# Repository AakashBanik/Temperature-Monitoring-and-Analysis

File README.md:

Temperature-Monitoring-and-Analysis

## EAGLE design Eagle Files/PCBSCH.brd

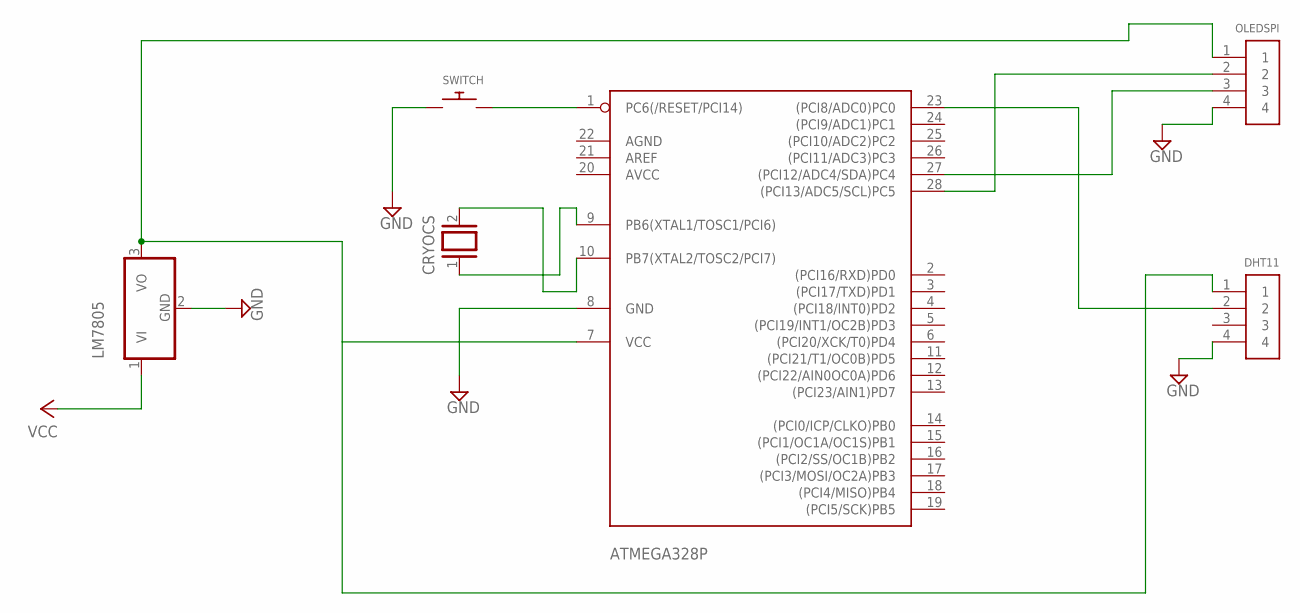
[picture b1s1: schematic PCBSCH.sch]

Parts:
ATMEGA328P: ATMEGA328PROUND; DIL28-3-ROUND
CRYOCS: XTAL/S; QS
DHT11: 1X4-BIG; 1X04-BIG
LM7805: 7805TV; TO220V
OLEDSPI: 1X4-BIG; 1X04-BIG
SWITCH: SWITCH_PUSHBUTTONSOFTTOUCHSMD_SJ; PUSHBUTTON_SMD_SJ

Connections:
GND: ATMEGA328P.8 (GND), DHT11.4, LM7805.2 (GND), OLEDSPI.4, SWITCH.P$1
unnamed: ATMEGA328P.7 (VCC), DHT11.1, LM7805.3 (VO), OLEDSPI.1
unnamed: ATMEGA328P.1 (PC6(/RESET/PCI14)), SWITCH.P$2
unnamed: ATMEGA328P.27 ((PCI12/ADC4/SDA)PC4), OLEDSPI.3
unnamed: ATMEGA328P.28 ((PCI13/ADC5/SCL)PC5), OLEDSPI.2
unnamed: ATMEGA328P.23 ((PCI8/ADC0)PC0), DHT11.2
unnamed: ATMEGA328P.9 (PB6(XTAL1/TOSC1/PCI6)), CRYOCS.1
unnamed: ATMEGA328P.10 (PB7(XTAL2/TOSC2/PCI7)), CRYOCS.2
VCC: LM7805.1 (VI)

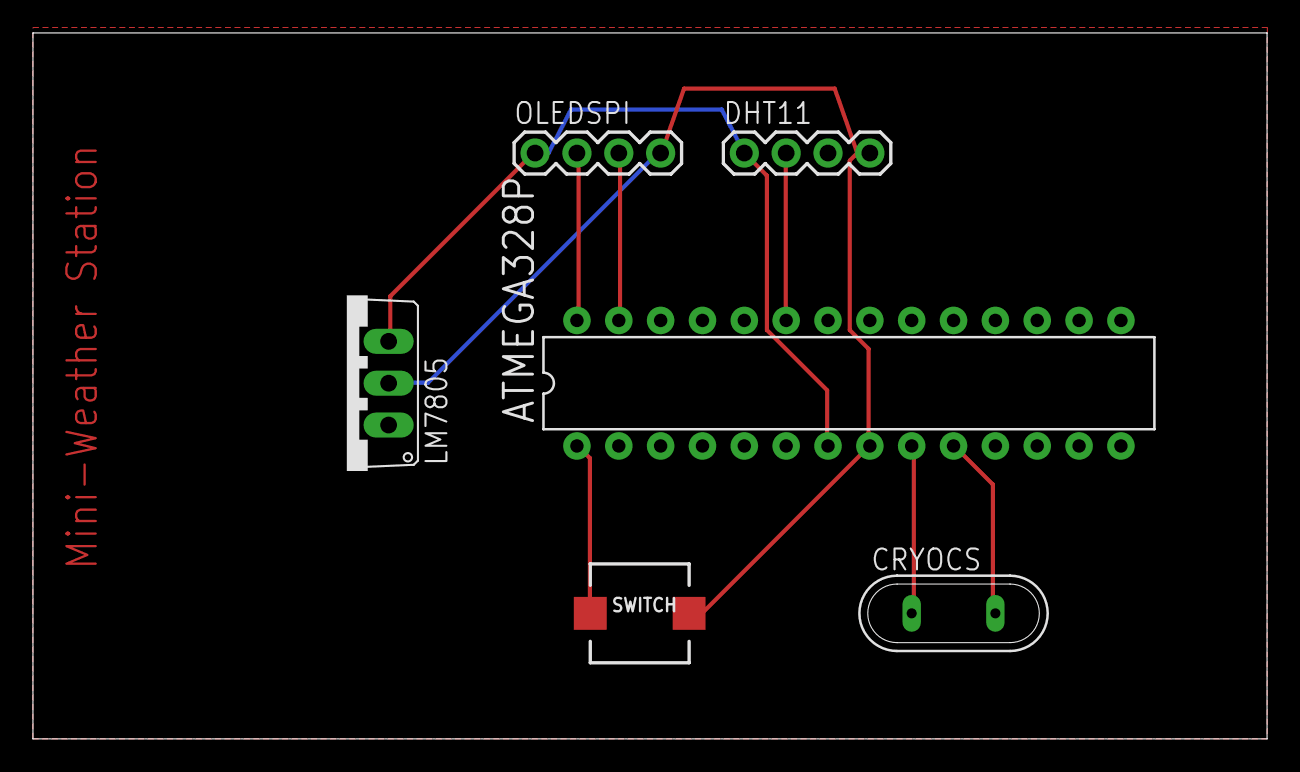
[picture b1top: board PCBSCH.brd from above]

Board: 2 copper layers, 74.9 x 42.8 mm, 6 parts (0 on the bottom side), 8 nets.

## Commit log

2018-12-04 Added arduino.c to upload to arduino
2018-12-04 Eagle files for schematics of hardware
